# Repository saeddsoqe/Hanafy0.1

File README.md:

# Hanafy 0.1

H 0.1
The H series is an open-source educational programmable circuit board powered by regular alkaline batteries. The H series is a safe, easy-to-use, platform for building projects in school at home or for fun

In this repo:
Schematic 
Layout
3D model
Bill Of Material
Graber file

Features
Version: H-0.1
ARM architecture.
ESP32 Dev Board. Dual core processor.  
Dimensions: 7.4cm * 7.2cm * 2cm

Built-in modules:
LDR (light sensor)
Push button *4
I/O pins *10
ON/OFF switch
RGB 
4 push buttons

Supports:
DC motor *2
Stepper motor *1

Power Supply: 
1.5V *4

Development environment:Block programming

Release date:March 2021
    Autodesk Eagle for schematic and layout design, and Fusion 360 for the 3D design.  

// Extra info
Supports:
  Wifi*
  Bluetooth*
  Servo motors 1
  They are connected with a pull up resistor*
version02: 
IoT capabilites

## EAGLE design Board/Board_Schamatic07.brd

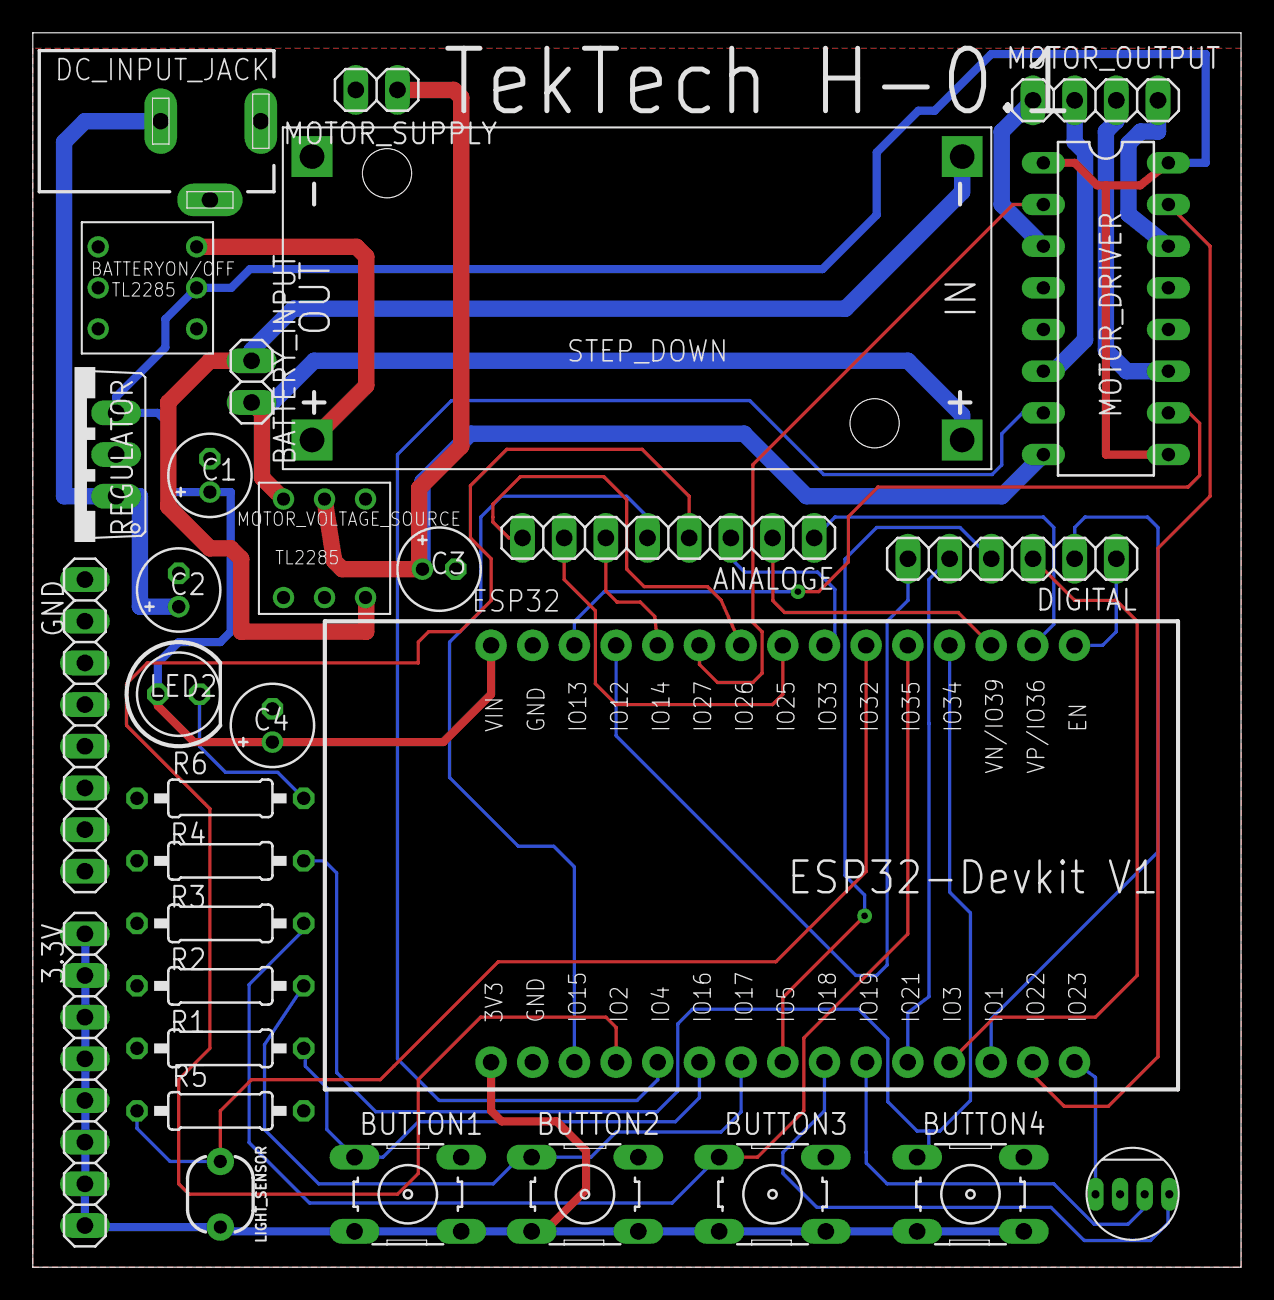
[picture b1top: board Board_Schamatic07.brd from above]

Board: 2 copper layers, 73.6 x 75.2 mm, 31 parts (0 on the bottom side), 39 nets.

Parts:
3.3V: 1X08
ANALOGE: 1X08
BATTERYON/OFF: TL2285; TL2285_PCB
BATTERY_INPUT: 1X02
BUTTON1, BUTTON2, BUTTON3, BUTTON4: B3F-10XX
C1, C3, C4: 100uf; E2-5
C2: 470uf; E2-5
DC_INPUT_JACK: DCJ0202
DIGITAL: 1X06
ESP32: ESP32DEVKITV1; ESP32-DEVKITV1
GND: 1X08
LED2: LED5MM
LIGHT_SENSOR: PHOTOCELLPTH; PHOTOCELL
MOTOR_DRIVER: L293D; DIL16
MOTOR_OUTPUT: 1X04
MOTOR_SUPPLY: 1X02
MOTOR_VOLTAGE_SOURCE: TL2285; TL2285_PCB
R1, R2, R3, R4, R5: 10k; 0207/10
R6: 220; 0207/10
REGULATOR: 7805TV; TO220V
RGB: LED-4_PIN
STEP_DOWN: DC-DC-STEP-DOWN-LM2596

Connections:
3.3V: 3.3V.1, 3.3V.2, 3.3V.3, 3.3V.4, 3.3V.5, 3.3V.6, 3.3V.7, 3.3V.8, BUTTON1.3, BUTTON1.4, BUTTON2.3, BUTTON2.4, BUTTON3.3, BUTTON3.4, BUTTON4.3, BUTTON4.4, ESP32.3V3, LIGHT_SENSOR.2
5-12V: C3.+, MOTOR_DRIVER.8, MOTOR_SUPPLY.2, MOTOR_VOLTAGE_SOURCE.2
5V: BATTERYON/OFF.2, C1.+, C4.+, ESP32.VIN, LED2.A, MOTOR_DRIVER.1, MOTOR_DRIVER.9, MOTOR_DRIVER.16, REGULATOR.3
+V: BATTERY_INPUT.1, MOTOR_VOLTAGE_SOURCE.3, STEP_DOWN.IN+
-V: BATTERY_INPUT.2, MOTOR_VOLTAGE_SOURCE.4, STEP_DOWN.IN-
A1CH0: ANALOGE.1, ESP32.D36
A1CH3: ANALOGE.2, ESP32.D39
A1CH5: ANALOGE.3, ESP32.D33
A2CH2: ANALOGE.4, ESP32.D2
A2CH3: ANALOGE.5, ESP32.D15
A2CH6: ANALOGE.6, ESP32.D14
A2CH8: ANALOGE.7, ESP32.D25
A2CH9: ANALOGE.8, ESP32.D26
BLUE: ESP32.D18, RGB.P$2
D1: DIGITAL.2, ESP32.D1
D3: DIGITAL.3, ESP32.D3
D5: DIGITAL.4, ESP32.D5
D12: DIGITAL.6, ESP32.D12
D21: DIGITAL.5, ESP32.D21
EN: DIGITAL.1, ESP32.EN
GND: C1.-, C2.-, C3.-, C4.-, DC_INPUT_JACK.1, DC_INPUT_JACK.2, ESP32.GND@1, ESP32.GND@2, GND.1, GND.2, GND.3, GND.4, GND.5, GND.6, GND.7, GND.8, MOTOR_DRIVER.4, MOTOR_DRIVER.5, MOTOR_DRIVER.12, MOTOR_DRIVER.13, MOTOR_SUPPLY.1, MOTOR_VOLTAGE_SOURCE.5, R1.2, R2.2, R3.2, R4.2, R5.2, R6.1, REGULATOR.2, RGB.P$5, STEP_DOWN.OUT-
GREEN: ESP32.D19, RGB.P$7
IN: C2.+, DC_INPUT_JACK.3, REGULATOR.1
IN1-1: ESP32.D27, MOTOR_DRIVER.2
IN1-2: ESP32.D4, MOTOR_DRIVER.7
IN2-1: ESP32.D22, MOTOR_DRIVER.15
IN2-2: ESP32.D13, MOTOR_DRIVER.10
unnamed: BATTERYON/OFF.3, STEP_DOWN.OUT+
unnamed: LED2.K, R6.2
unnamed: BUTTON3.1, ESP32.D35, R3.1
unnamed: BUTTON4.1, ESP32.D34, R4.1
unnamed: ESP32.D32, LIGHT_SENSOR.1, R5.1
unnamed: BUTTON1.1, ESP32.D16, R1.1
unnamed: BUTTON2.1, ESP32.D17, R2.1
O1-1: MOTOR_DRIVER.3, MOTOR_OUTPUT.4
O1-2: MOTOR_DRIVER.6, MOTOR_OUTPUT.3
O2-1: MOTOR_DRIVER.14, MOTOR_OUTPUT.1
O2-2: MOTOR_DRIVER.11, MOTOR_OUTPUT.2
RED: ESP32.D23, RGB.P$1

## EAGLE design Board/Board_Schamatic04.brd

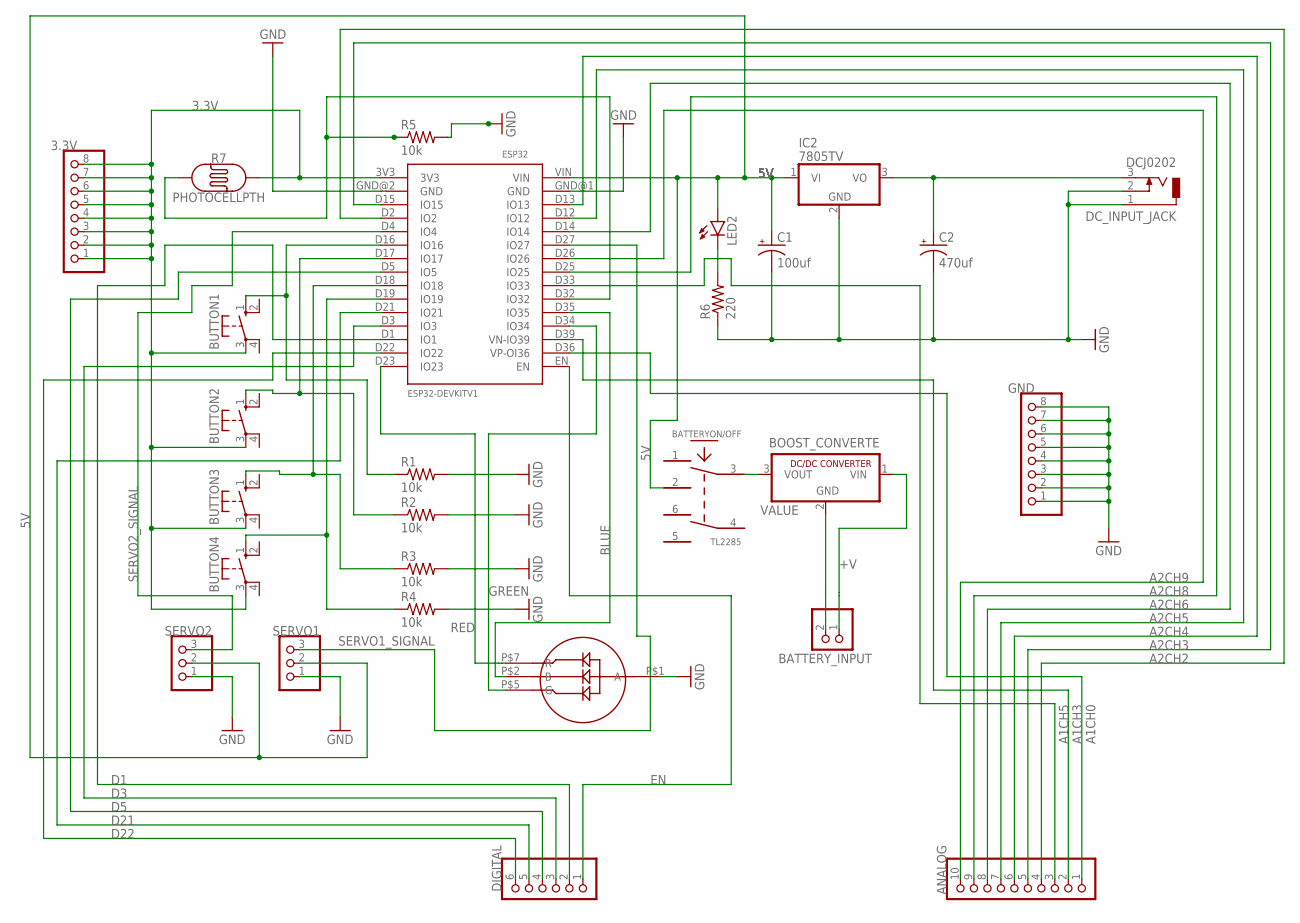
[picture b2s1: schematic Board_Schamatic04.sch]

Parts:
3.3V: PINHD-1X8; 1X08
ANALOG: PINHD-1X10; 1X10
BATTERYON/OFF: TL2285; TL2285_PCB
BATTERY_INPUT: PINHD-1X2; 1X02
BOOST_CONVERTE: R-78C1.8-1.0; SIP3
BUTTON1, BUTTON2, BUTTON3, BUTTON4: 10-XX; B3F-10XX
C1: 100uf; E2-5
C2: 470uf; E2-5
DC_INPUT_JACK: DCJ0202
DIGITAL: PINHD-1X6; 1X06
ESP32: ESP32DEVKITV1; ESP32-DEVKITV1
GND: PINHD-1X8; 1X08
IC2: 7805TV; TO220V
LED2: LED5MM
LED-4_PIN1: LED-4_PIN
R1, R2, R3, R4, R5: 10k; 0207/10
R6: 220; 0207/10
R7: PHOTOCELLPTH; PHOTOCELL
SERVO1, SERVO2: PINHD-1X3; 1X03

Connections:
3.3V: 3.3V.1, 3.3V.2, 3.3V.3, 3.3V.4, 3.3V.5, 3.3V.6, 3.3V.7, 3.3V.8, BUTTON1.3, BUTTON2.3, BUTTON3.3, BUTTON4.3, ESP32.3V3, R7.2
5V: BATTERYON/OFF.2, C1.+, ESP32.VIN, IC2.1 (VI), LED2.A, SERVO1.2, SERVO2.2
+V: BATTERY_INPUT.1, BOOST_CONVERTE.1 (VIN)
A1CH0: ANALOG.1, ESP32.D36 (VP-OI36)
A1CH3: ANALOG.2, ESP32.D39 (VN-IO39)
A1CH5: ANALOG.3, ESP32.D33 (IO33)
A2CH2: ANALOG.4, ESP32.D2 (IO2)
A2CH3: ANALOG.5, ESP32.D15 (IO15)
A2CH4: ANALOG.6, ESP32.D13 (IO13)
A2CH5: ANALOG.7, ESP32.D12 (IO12)
A2CH6: ANALOG.8, ESP32.D14 (IO14)
A2CH8: ANALOG.9, ESP32.D25 (IO25)
A2CH9: ANALOG.10, ESP32.D26 (IO26)
BLUE: ESP32.D35 (IO35), LED-4_PIN1.P$2 (B)
D1: DIGITAL.2, ESP32.D1 (IO1)
D3: DIGITAL.3, ESP32.D3 (IO3)
D5: DIGITAL.4, ESP32.D5 (IO5)
D21: DIGITAL.5, ESP32.D21 (IO21)
D22: DIGITAL.6, ESP32.D22 (IO22)
EN: DIGITAL.1, ESP32.EN
GND: C1.-, C2.-, DC_INPUT_JACK.1, DC_INPUT_JACK.2, ESP32.GND@1 (GND), ESP32.GND@2 (GND), GND.1, GND.2, GND.3, GND.4, GND.5, GND.6, GND.7, GND.8, IC2.2 (GND), LED-4_PIN1.P$1 (A), R1.2, R2.2, R3.2, R4.2, R5.2, R6.1, SERVO1.1, SERVO2.1
GREEN: ESP32.D34 (IO34), LED-4_PIN1.P$5 (G)
unnamed: BATTERYON/OFF.3, BOOST_CONVERTE.3 (VOUT)
unnamed: C2.+, DC_INPUT_JACK.3, IC2.3 (VO)
unnamed: LED2.K (C), R6.2
unnamed: BATTERY_INPUT.2, BOOST_CONVERTE.2 (GND)
unnamed: ESP32.D32 (IO32), R5.1, R7.1
unnamed: BUTTON1.1 (S), ESP32.D16 (IO16), R1.1
unnamed: BUTTON2.1 (S), ESP32.D17 (IO17), R2.1
unnamed: BUTTON3.1 (S), ESP32.D18 (IO18), R3.1
unnamed: BUTTON4.1 (S), ESP32.D19 (IO19), R4.1
RED: ESP32.D23 (IO23), LED-4_PIN1.P$7 (R)
SERVO1_SIGNAL: ESP32.D27 (IO27), SERVO1.3
SERVO2_SIGNAL: ESP32.D4 (IO4), SERVO2.3

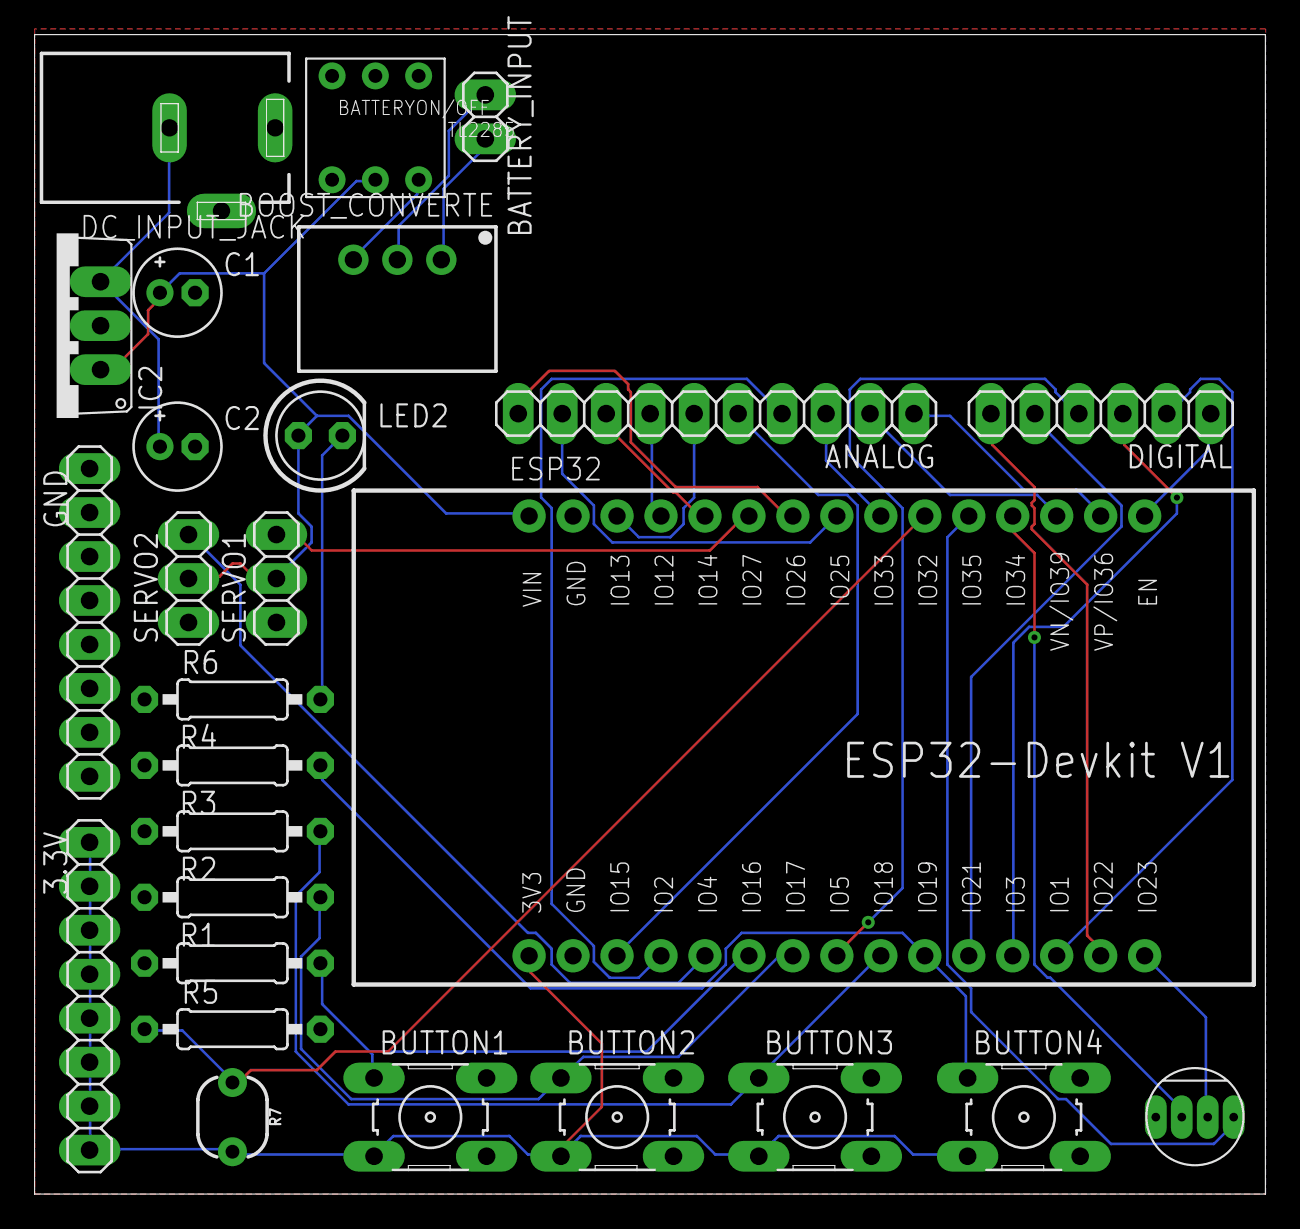
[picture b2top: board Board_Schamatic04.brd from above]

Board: 2 copper layers, 71.1 x 67.0 mm, 27 parts (0 on the bottom side), 34 nets.

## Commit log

2021-01-24 Create Push_Buttons
2021-01-30 Create Board
2021-02-08 Rename Dinstructions.txt to instructions.txt

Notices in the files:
parts and their libraries:
SparkFun-Sensors: Licensing: Creative Commons ShareAlike 4.0 International - https://creativecommons.org/licenses/by-sa/4.0
diy-modules: Released under the Creative Commons Attribution 4.0 International License: http://creativecommons.org/licenses/by/4.0
